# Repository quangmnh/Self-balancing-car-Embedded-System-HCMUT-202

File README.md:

# Abstract

We are making a Self-balancing robot taking inspiration from Wouter Klop's project

https://gitlab.com/kloppertje/balancingrobot

Report:

https://www.overleaf.com/project/60979d68228ff94e5ad1fe6f

# Weekly Plan
## Week 20 
- [ ] Add the detail design
- [ ] FIND WAYS TO EVALUATE THE SYSTEMS (Calculate the value, the max velocity of the bot, the max angle of the slope)

## Week 19
- [x] Creating report 
- [x] Modelling the system
- [ ] Assemble the parts (Only the capacitor left)
- [x] Additional hardware acquisition
- [ ] Porting it to the hardware.

## Week 16

- [ ] Calculation
  + Torque
  + MPU-6050 returned value processing  
  + Body balancing factor (Applied mechanics lul)
- [x] Sttat machine
- [ ] Re-design some body part.
- [ ] Get PCB and assemble all parts 
- [x] Initiate the report.

## Week 15

- ~~Prototyping some body part for experiment.~~
- ~~Enlisting full electrical components with their price tag.~~
- ~~Buy the electrical components~~
- Initial calculation
  + Torque
  + ~~Power consumption~~
  + MPU-6050 returned value processing  
  + Body balancing factor (Applied mechanics lul)
- Re-design some body part.
- ~~PCB order (JLCPCB maybe)~~

# Expenditure and Notes

https://docs.google.com/spreadsheets/d/1sYImMAOnU2ea2EhUiEneGWEZ3-_E23mFMH0feFGn73Y/edit?ts=607518ca#gid=1386834576

# Contents

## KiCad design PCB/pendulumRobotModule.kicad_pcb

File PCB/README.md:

This folder contains KiCad (5.0.0) design files for the BalancingRobot PCB. 

# Features
* Supports both DRV8825 and A4988 based stepper drivers. Should also be compatible with TMC2100 (with settings configurable via ESP32), not tested yet though.
* Supported voltage: ~7 - 24V (2-6S LiPo/Li-ion)
* Digital current control of steppers (you'll need to desolder the potmeter and add a wire)
* Dynamic microstep switching, allowing for insane speeds
* Connections: 
	- Digital RC receiver (I use IBus / FlySky protocol), J5 upper row
	- Servo, J5 middle row. In case you want to add an arm for self righting :).
	- Digital LED (Neopixel / WS2812B etc), J5, lower row
	- All unused ESP32 pins are broken out (including I2C), for further use and development (J2)
	- Power input (J3). Allows for both a screw clamp and direct wire soldering. I prefer the last, given the high power output of a LiPo in case something comes loose.
* Wireless parameter tuning and data plotting. Makes tuning the controllers a lot easier
* Websocket communication for real-time communication between ESP32 and browser
* Web interface via access point / WiFi network. SSID and key can be set via web interface.

# Assembly
Assembly is quite straightforward. For those who like some instructions, here goes. For the ones that don't like to follow instructions: that's ok, but please read the last instruction about adjusting the buck converter voltage.

1. Start with the SMD components on the bottom side. First, pre-tin one pad, then place the SMD component while reheating the first pad. Finally, solder the second pad. C5 is not mounted.
2. Next, mount the voltage regulator module U3. Use some wires to connect the 4 pads to the PCB.
3. Place the IMU (U2) with the angled male and female headers. Make sure that the IMU is rigidly mounted. If you don't, the IMU might for example vibrate during operation, causing unstable behaviour. See below pictures for clarification.
4. Add all female headers (J1, J4, J7, and for the stepper driver and ESP32 modules). Optionally, place some headers on J5 and J2 if you like.
5. Finally, place C2, C4 and F1.

IMPORTANT: adjust the voltage regulator to 5V BEFORE inserting any modules. By default, the voltage regulator is set to a higher voltage, and if you don't adjust it, you'll fry some components. 

IMU mounting

In the end, the PCB should look something like this

## Advanced
Some optional improvements are listed here, which are not required for basic operation. 

You can de-solder the current adjustment potentiometer on the stepper driver breakout boards. Add a wire to the wiper terminal, and connect the (two) wires to J4. Current can then be adjusted via the web interface. Or, get creative, and implement some current saving functionality.

For better performance, you can tie the decay mode pin of the DRV8825 to VCC, setting it in fast mode. The DRV8825 sometimes skips steps in slow/mixed decay mode. Below picture illustrates both improvements.

## Auxiliary header
Connector J2 has a grid of 12 pins (3x4), with some general pins broken out, together with all unused ESP32 IO pins. See the close-up of the header below. Pin numbering in this picture is used in the table below to identify pins.

//

| Pin # | Name    | ESP32 pin |
|-------|---------|-----------|
| 1     | 5V      | Vin       |
| 2     | IMU_SCL | D22       |
| 3     | IMU_SDA | D21       |
| 4     | GND     | GND       |
| 5     | AUX1    | D32       |
| 6     | AUX2    | D33       |
| 7     | GND     | GND       |
| 8     | AUX3    | D35       |
| 9     | AUX4    | D26       |
| 10    | VCC     | 3V3       |
| 11    | AUX5    | D39       |
| 12    | AUX6    | D36       |

# BOM
Applicable for v1.1. v1.0 doesn't have R7.

| Qty | Reference(s)           | Value                                    |
|-----|------------------------|------------------------------------------|
| 2   | A1, A2                 | DRV8825 / A4988 stepper driver breakout  |
| 2   | C1, C3                 | 1u capacitor, 0805 SMD                   |
| 2   | C2, C4                 | 100u elco                                |
| 1   | C5                     | 100n capacitor, not placed               |
| 1   | F1                     | Polyfuse                                 |
| 1   | J1                     | Female header, cut to size               |
| 1   | J2                     | N/A, solder whatever you like here       |
| 1   | J3                     | Screw terminal, or solder wires directly |
| 2   | J4, J7                 | 4 pin (fe)male header, cut to size       |
| 1   | J5                     | Male header, cut to size                 |
| 6   | R1, R2, R3, R4, R6, R7 | 3k3 resistor, 0805 SMD                   |
| 1   | R5                     | 100k resistor, 0805 SMD                  |
| 1   | U1                     | ESP32 devKit module, 30 pins             |
| 1   | U2                     | MPU6050 breakout, 8 pins                 |
| 1   | U3                     | Buck converter module                    |

Additionally, you'll need a pair of 8 pin male/female angled headers, for mounting the IMU. For mounting the ESP32 and stepper driver modules, you'll need 2 times 15 and 16 pin female headers (4 in total).

Some examples of the modules:
* [ESP32 Devkit V1 module, 30 pins](https://www.aliexpress.com/item/ESP32-Development-Board-WiFi-Bluetooth-Ultra-Low-Power-Consumption-Dual-Core-ESP-32-ESP-32S/32802431728.html?spm=a2g0s.9042311.0.0.26604c4dM62q0I)
* [DRV8825 stepper driver](https://www.aliexpress.com/item/Free-shipping-10pcs-lot-3D-Printer-StepStick-DRV8825-Stepper-Motor-Drive-Carrier-Reprap-4-layer-PCB/32292074706.html?spm=a2g0s.9042311.0.0.26604c4dM62q0I)
* [MPU6050 IMU](http://www.aliexpress.com/item/GY-521-MPU-6050-MPU6050-Module-3-Axis-analog-gyro-sensors-3-Axis-Accelerometer-Module/32340949017.html?spm=a2g0s.9042311.0.0.26604c4dM62q0I)
* [Buck converter](https://www.aliexpress.com/item/10PCS-Mini-3A-DC-DC-Converter-Step-Down-Module-Adjustable-3V-5V-16V-Power-for-RC/32639738406.html?spm=a2g0s.9042311.0.0.66ef4c4duolobi)

# Issues
For PCB version 1.0, the + and - signs of the RX/Servo/LED indicator are swapped. The pinout is correct though. To be clear, the order (from right to left) is -, +, and signal. This has been solved in v1.1.

# Change history
## v1.0 
Initial version
## v1.1
* Increased track width of 5V and 24V traces
* Added second via in 24V trace, or rather added trace to second via which wasn't there in v1.0
* Swapped + and - symbols on silkscreen close to RX header 
* Added a 10k pull-up on the stepper driver enable. In v1.0, no pull-up is present, meaning the steppers are enabled if the ESP32 isn't running. No big deal, but somewhat neater to disable steppers if the ESP32 isn't running.
## v1.2
* Added optional 100k RX pulldown resistor
* Added optional 5V filtering cap (might be useful if for example some Neopixels are connected to 5V line)
* Added some markings for the buck converter, clarifying the mounting direction
* Added connections for (fused) battery voltage (J6)

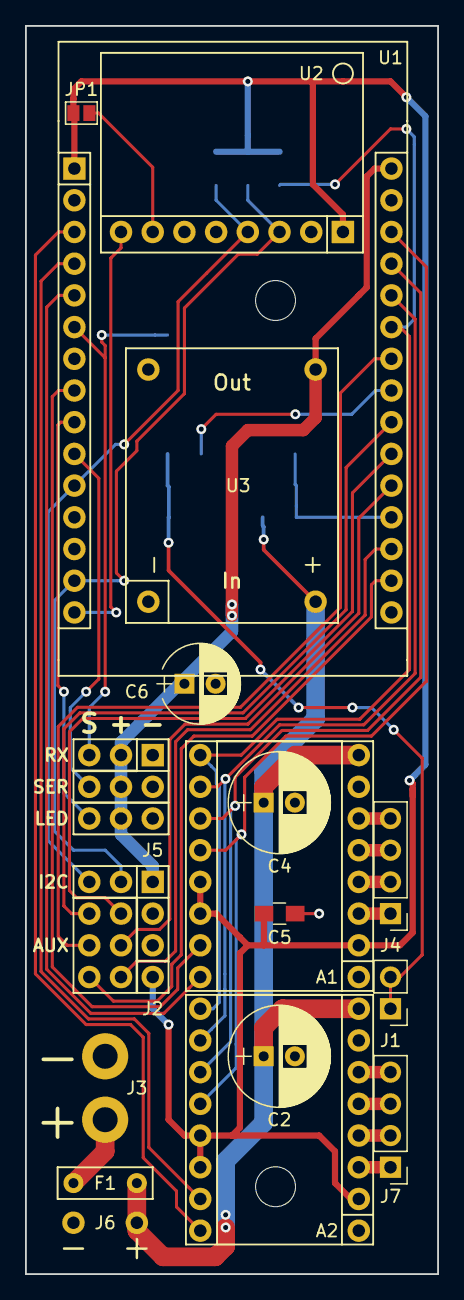
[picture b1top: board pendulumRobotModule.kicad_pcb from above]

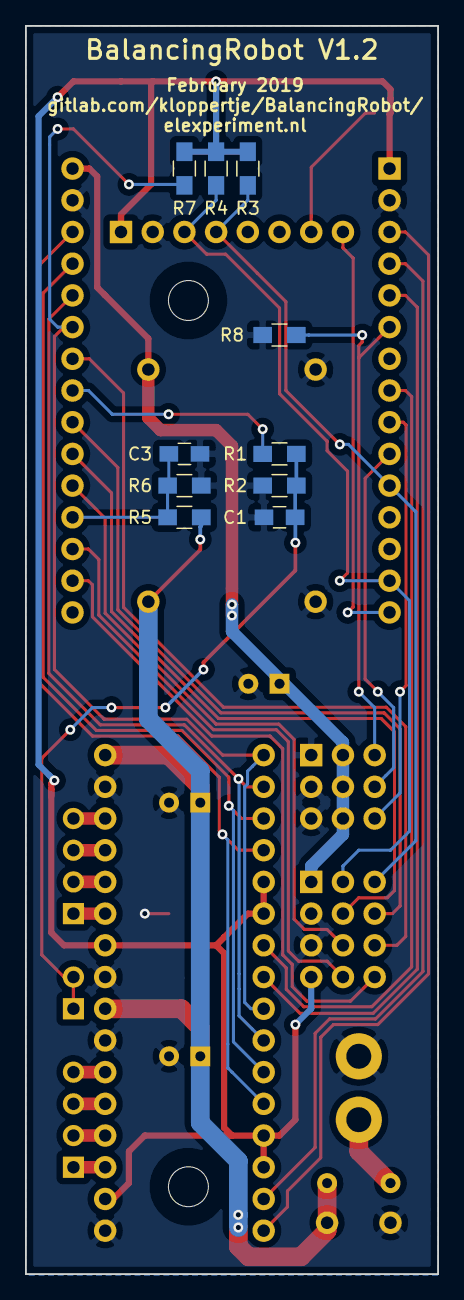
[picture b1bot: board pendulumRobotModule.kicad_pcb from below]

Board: 2 copper layers, 33.0 x 100.0 mm, 28 parts (10 on the bottom side), 37 nets.

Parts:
A1, A2: Pololu_Breakout_DRV8825; DRV8825-breakout
C1, C3: 1u; C_0805_HandSoldering
C2, C4: 100u; CP_Radial_D8.0mm_P2.50mm
C5: 100n; C_0805_HandSoldering
C6: 470u; CP_Radial_D6.3mm_P2.50mm
F1: Polyfuse; polyfuse-5.08mm
J1: Conn_01x02_Female; Socket_Strip_Straight_1x02_Pitch2.54mm
J2: conn_3x4; pinHeader_3x4
J3: Conn_01x02_Male; wirePad-2x-2mm
J4, J7: Conn_01x04_Female; Socket_Strip_Straight_1x04_Pitch2.54mm
J5: conn_3x3; pinHeader_3x3
J6: Conn_01x02_Male; pinHeader_2x1_5.08mm
JP1: Jumper; GS2
R1, R2, R3, R4, R6, R7: 3k3; R_0805_HandSoldering
R5, R8: 100k; R_0805_HandSoldering
U1: ESP32-devKit; ESP32-devkit-30p
U2: MPU6050-breakout; MPU6050-breakout-angledHeader
U3: buckConverter-adj; buck-converter-adj

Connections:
+5V: C6.1, J2.1, J5.2, J5.5, J5.8, U1.30, U3.3
+24V: A1.8, A2.8, C2.1, C4.1, F1.1, J6.1, R5.1, U3.2
/AUX1: J2.5, U1.21
/AUX2: J2.6, U1.22
/AUX3: J2.8, U1.20
/AUX4: J2.9, U1.24
/AUX5: J2.11, U1.18
/AUX6: J2.12, U1.17
/BATT_VOLT: C3.1, R5.2, R6.1, U1.19
/DAC1: R1.1, U1.23
/IBUS_RX: J5.3, R8.1, U1.6
/IMU_INT: U1.15, U2.8
/IMU_SCL: J2.2, R4.2, U1.14, U2.3
/IMU_SDA: J2.3, R3.2, U1.11, U2.4
/LED_DATA: J5.9, U1.9
/SERVO_PWM: J5.6, U1.10
/motADir: A1.16, U1.5
/motAStp: A1.15, U1.8
/motBDir: A2.16, U1.3
/motBStp: A2.15, U1.4
/motEn: A1.9, A2.9, R7.2, U1.25
/uStep0: A1.10, A2.10, U1.26
/uStep1: A1.11, A2.11, U1.27
/uStep2: A1.12, A2.12, U1.28
GND: A1.1, A1.7, A2.1, A2.7, C1.2, C2.2, C3.2, C4.2, C5.2, C6.2, J2.4, J2.7, J3.2, J5.1, J5.4, J5.7, J6.2, R2.2, R6.2, R8.2, U1.2, U1.29, U2.2, U3.1, U3.4
unnamed: A1.3, J4.1
unnamed: A1.4, J4.2
unnamed: A1.5, J4.3
unnamed: A1.6, J4.4
unnamed: A2.3, J7.1
unnamed: A2.4, J7.2
unnamed: A2.5, J7.3
unnamed: A2.6, J7.4
unnamed: C1.1, J1.1, J1.2, R1.2, R2.1
unnamed: F1.2, J3.1
unnamed: JP1.2, U2.7
VCC: A1.2, A1.13, A1.14, A2.2, A2.13, A2.14, C5.1, J2.10, JP1.1, R3.1, R4.1, R7.1, U1.1, U2.1

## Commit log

2021-04-13 Add Block Diagram of the system
2021-04-14 test the overleaf linking thing
2021-04-16 pcb and body
2021-04-20 sum anal
2021-05-09 Update main.cpp
    Fix M_PI constant error and the union typedef
2021-05-09 Adding the state and adding new functions
2021-05-09 Adding flowchart
2021-05-09 Add state machine for the system
2021-05-15 motor_test and gcode
